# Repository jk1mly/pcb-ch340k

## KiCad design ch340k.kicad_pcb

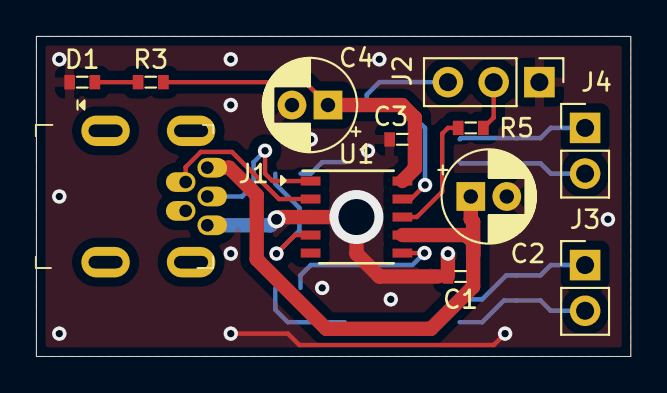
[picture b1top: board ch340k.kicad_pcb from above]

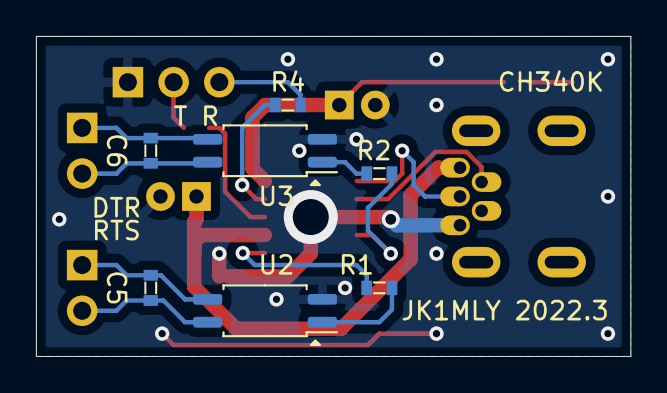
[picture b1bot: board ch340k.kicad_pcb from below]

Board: 2 copper layers, 33.0 x 17.8 mm, 19 parts (7 on the bottom side), 18 nets.

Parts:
C1, C1#2, C1#3, C3: 0.1u; 0603
C2, C4: 10u; CP_Radial_D5.0mm_P2.00mm
D1: LED; 0603
J1: USB_B_Mini; USB_Mini_B_Female_aki
J2: Conn_01x03_Male; PinHeader_1x03_P2.54mm_Vertical
J3, J4: Conn_01x02_Male; PinHeader_1x02_P2.54mm_Vertical
R1, R2, R3, R4, R5: 1k; 0603
U1: CH340K; SSOP-10_3.9x4.9mm_P1.00mm
U2, U3: TLP290; SOP-4_4.4x2.6mm_P1.27mm

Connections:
GND: C1.2, C2.2, C3.2, C4.2, D1.1 (K), J1.5 (GND), J2.1, U1.3 (GND), U2.2, U3.2
unnamed: C3.1, C4.1, R3.1, U1.10 (V3)
unnamed: C1#3.1, J3.2, U2.4
unnamed: C1#3.2, J3.1, U2.3
unnamed: C1#2.1, J4.2, U3.4
unnamed: C1#2.2, J4.1, U3.3
unnamed: D1.2 (A), R3.2
unnamed: C1.1, C2.1, J1.1 (VBUS), U1.7 (VCC)
unnamed: J1.2 (D-), U1.2 (UD-)
unnamed: J1.3 (D+), U1.1 (UD+)
unnamed: R1.2, U2.1
unnamed: R2.2, U3.1
unnamed: J2.3, R4.2
unnamed: J2.2, R5.2
unnamed: R2.1, U1.4 (~DTR)
unnamed: R1.1, U1.6 (~RTS)
unnamed: R5.1, U1.8 (TXD)
unnamed: R4.1, U1.9 (RXD)

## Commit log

2022-03-19 prototype
2022-03-19 M5Stamp/ESP32 Downloader prototype
2022-03-19 CW Interface prototype
2022-05-03 Add files via upload
    秋月の通販コード追加
    部品表の代わりにxmlファイル
